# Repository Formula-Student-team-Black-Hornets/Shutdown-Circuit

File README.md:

# Shutdown Circuit Board

## Dimensions
* **Height:** 91.00 [mm]
* **Length:** 56.15 [mm]
* **Width:** ? [mm]

## Power supply
* **Voltage:** [V]
* **Current (max):** [A]
* **Current (min):** [A]
* **Current (avg):** [A]
* **Power:** [W]

## Connections

### J1
* **X.1** `[DOUT]` SDC_OUT
* **X.2** `[GND]`  GND
* **X.3** `[DIN]`  SDC_IN
* **X.3** `[GND]`  GND

### J2
* **X.1** `[DIN]`  RESET
* **X.2** `[VCC]`  12V
* **X.3** `[N.C]`  N.C
* **X.4** `[GND]`  GND

### J3
* **X.1** `[DOUT]` IMD_DASHBOARD
* **X.2** `[DOUT]` GND
* **X.3** `[DOUT]` AMS_DASHBOARD
* **X.4** `[DOUT]` GND

### J4
* **X.1** `[DIN]`  IMD_OkHS
* **X.2** `[GND]`  GND
* **X.3** `[DIN]`  BSPD
* **X.4** `[GND]`  GND

### J5
* **X.1** `[DIN]`  AMS_DISCHARGE_ENABLE
* **X.2** `[GND]`  GND
* **X.3** `[DIN]`  TSAL
* **X.4** `[GND]`  GND

### J6
* **X.1** `[VCC]`  12V
* **X.2** `[GND]`  GND
* **X.3** `[VCC]`  12V
* **X.4** `[GND]`  GND

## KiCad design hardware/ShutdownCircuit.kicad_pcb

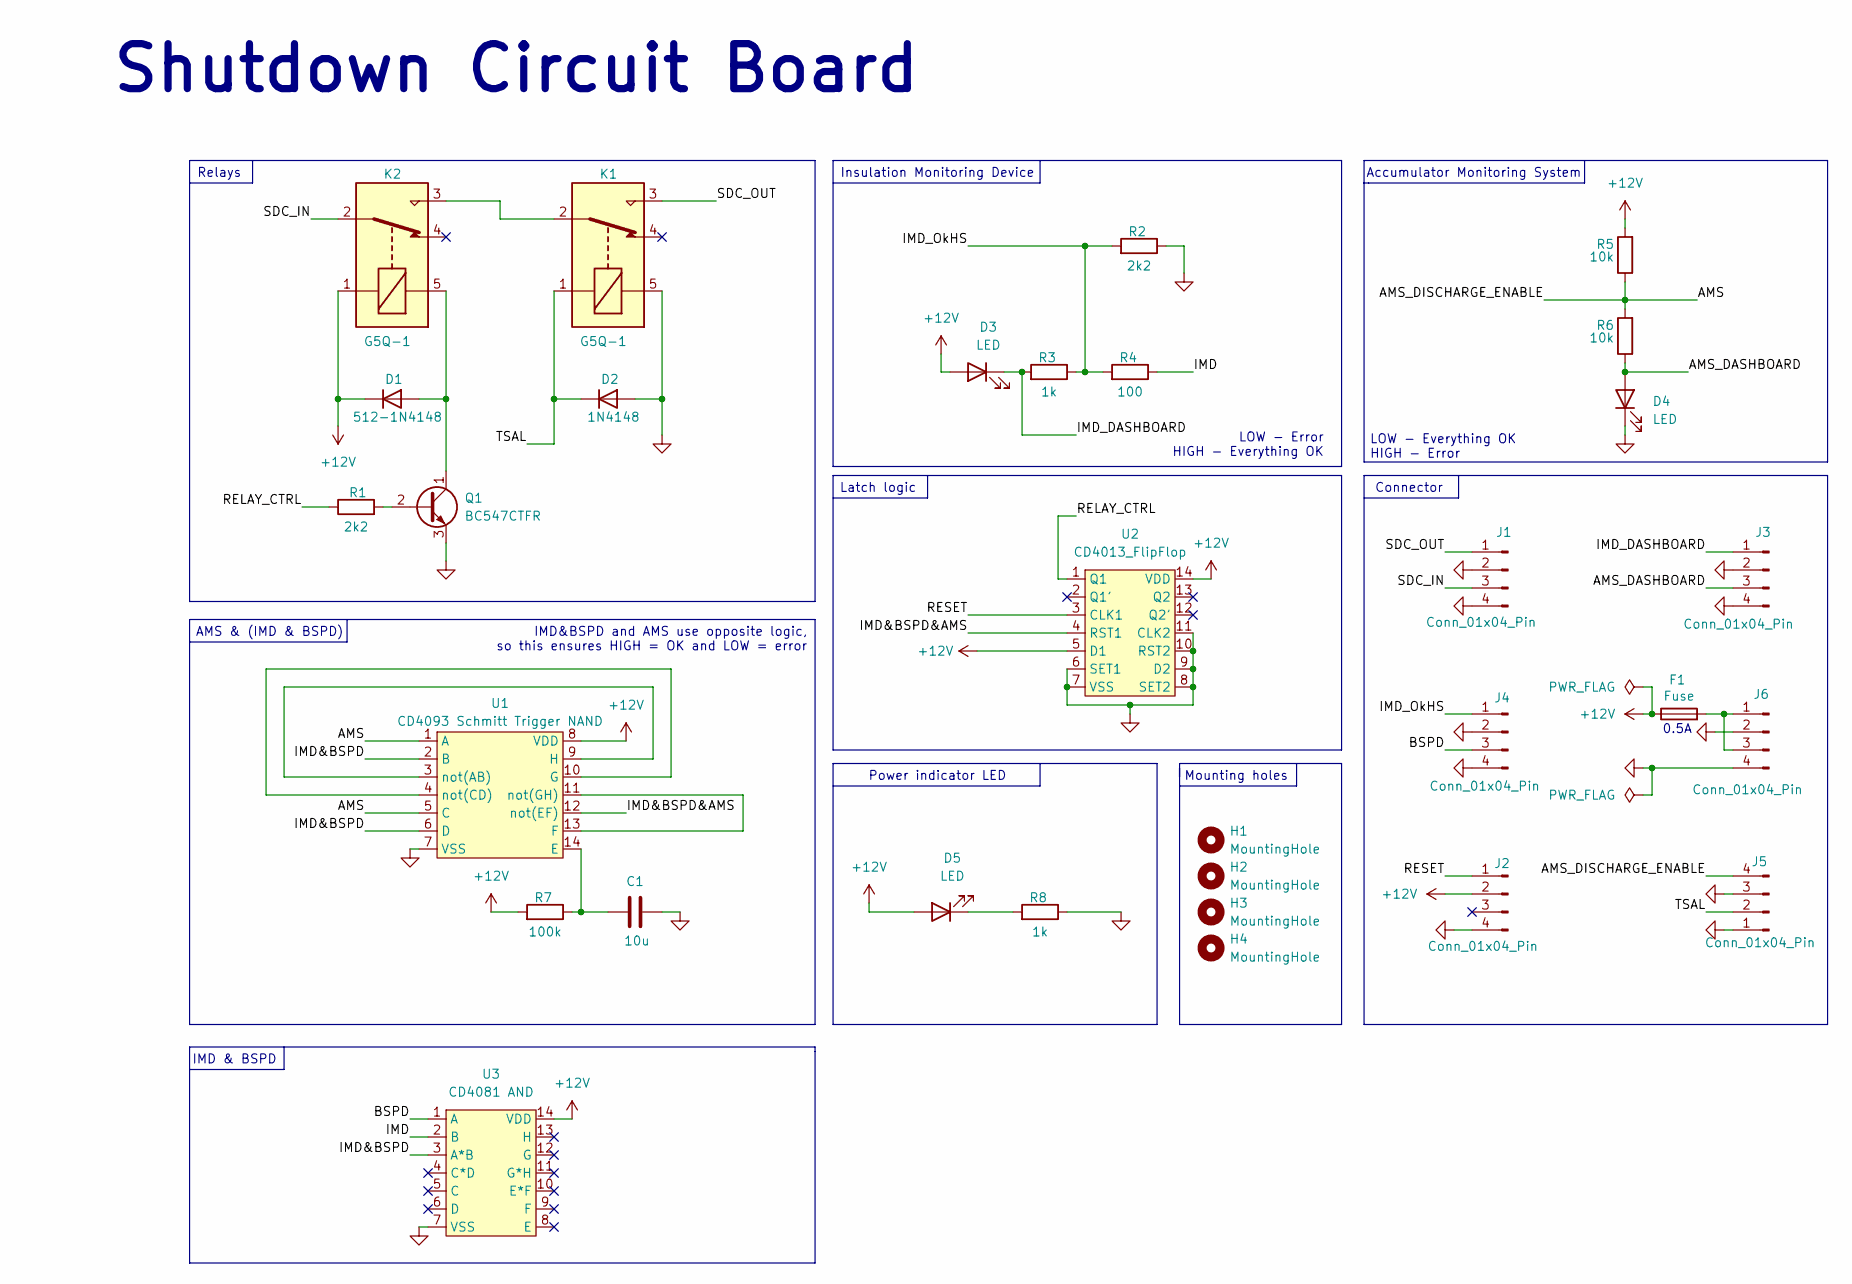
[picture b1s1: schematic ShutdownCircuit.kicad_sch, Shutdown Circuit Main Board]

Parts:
C1: 10u; C_1206_3216Metric_Pad1.33x1.80mm_HandSolder
D1: 512-1N4148; D_1206_3216Metric_Pad1.42x1.75mm_HandSolder
D2: 1N4148; D_1206_3216Metric_Pad1.42x1.75mm_HandSolder
D3, D4, D5: LED; LED_1206_3216Metric_Pad1.42x1.75mm_HandSolder
F1: Fuse; Fuse_1206_3216Metric_Pad1.42x1.75mm_HandSolder
H1, H2, H3, H4: MountingHole; MountingHole_2.1mm
J1, J2, J3, J4, J5, J6: Conn_01x04_Pin; Molex_Micro-Fit_3.0_43650-0400_1x04_P3.00mm_Horizontal
K1, K2: G5Q-1; Relay_SPDT_Omron-G5Q-1
Q1: BC547CTFR; TO-92_Inline
R1, R2: 2k2; R_1206_3216Metric_Pad1.30x1.75mm_HandSolder
R3, R8: 1k; R_1206_3216Metric_Pad1.30x1.75mm_HandSolder
R4: 100; R_1206_3216Metric_Pad1.30x1.75mm_HandSolder
R5, R6: 10k; R_1206_3216Metric_Pad1.30x1.75mm_HandSolder
R7: 100k; R_1206_3216Metric_Pad1.30x1.75mm_HandSolder
U1: CD4093 Schmitt Trigger NAND; SOIC-14_3.9x8.7mm_P1.27mm
U2: CD4013_FlipFlop; SOIC-14_3.9x8.7mm_P1.27mm
U3: CD4081 AND; SOIC-14_3.9x8.7mm_P1.27mm

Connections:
+12V: D1.1 (K), D3.2 (A), D5.2 (A), F1.1, J2.2, K2.1, R5.2, R7.2, U1.8 (VDD), U2.5 (D1), U2.14 (VDD), U3.14 (VDD)
/AMS: J5.4, R5.1, R6.2, U1.1 (A), U1.5 (C)
/AMS_DASHBOARD: D4.2 (A), J3.3, R6.1
/BSPD: J4.3, U3.1 (A)
/IMD: R4.1, U3.2 (B)
/IMD&BSPD: U1.2 (B), U1.6 (D), U3.3 (A*B)
/IMD&BSPD&AMS: U1.12 (not(EF)), U2.4 (RST1)
/IMD_DASHBOARD: D3.1 (K), J3.1, R3.2
/IMD_OkHS: J4.1, R2.2, R3.1, R4.2
/RELAY_CTRL: R1.1, U2.1 (Q1)
/RESET: J2.1, U2.3 (CLK1)
/SDC_IN: J1.3, K2.2
/SDC_OUT: J1.1, K1.3
/TSAL: D2.1 (K), J5.2, K1.1
GND: C1.2, D2.2 (A), D4.1 (K), J1.2, J1.4, J2.4, J3.2, J3.4, J4.2, J4.4, J5.1, J5.3, J6.2, J6.4, K1.5, Q1.3 (E), R2.1, R8.1, U1.7 (VSS), U2.6 (SET1), U2.7 (VSS), U2.8 (SET2), U2.9 (D2), U2.10 (RST2), U2.11 (CLK2), U3.7 (VSS)
unnamed: D1.2 (A), K2.5, Q1.1 (C)
unnamed: D5.1 (K), R8.2
unnamed: F1.2, J6.1, J6.3
unnamed: K1.2, K2.3
unnamed: Q1.2 (B), R1.2
unnamed: C1.1, R7.1, U1.14 (E)
unnamed: U1.11 (not(GH)), U1.13 (F)
unnamed: U1.4 (not(CD)), U1.10 (G)
unnamed: U1.3 (not(AB)), U1.9 (H)

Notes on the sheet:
0.5A
Insulation Monitoring Device
Shutdown Circuit Board
LOW - Everything OK HIGH - Error
Relays
Connector
IMD&BSPD and AMS use opposite logic, so this ensures HIGH = OK and LOW = error
Mounting holes
Latch logic
AMS & (IMD & BSPD)
LOW - Error HIGH - Everything OK
IMD & BSPD
Power indicator LED
Accumulator Monitoring System

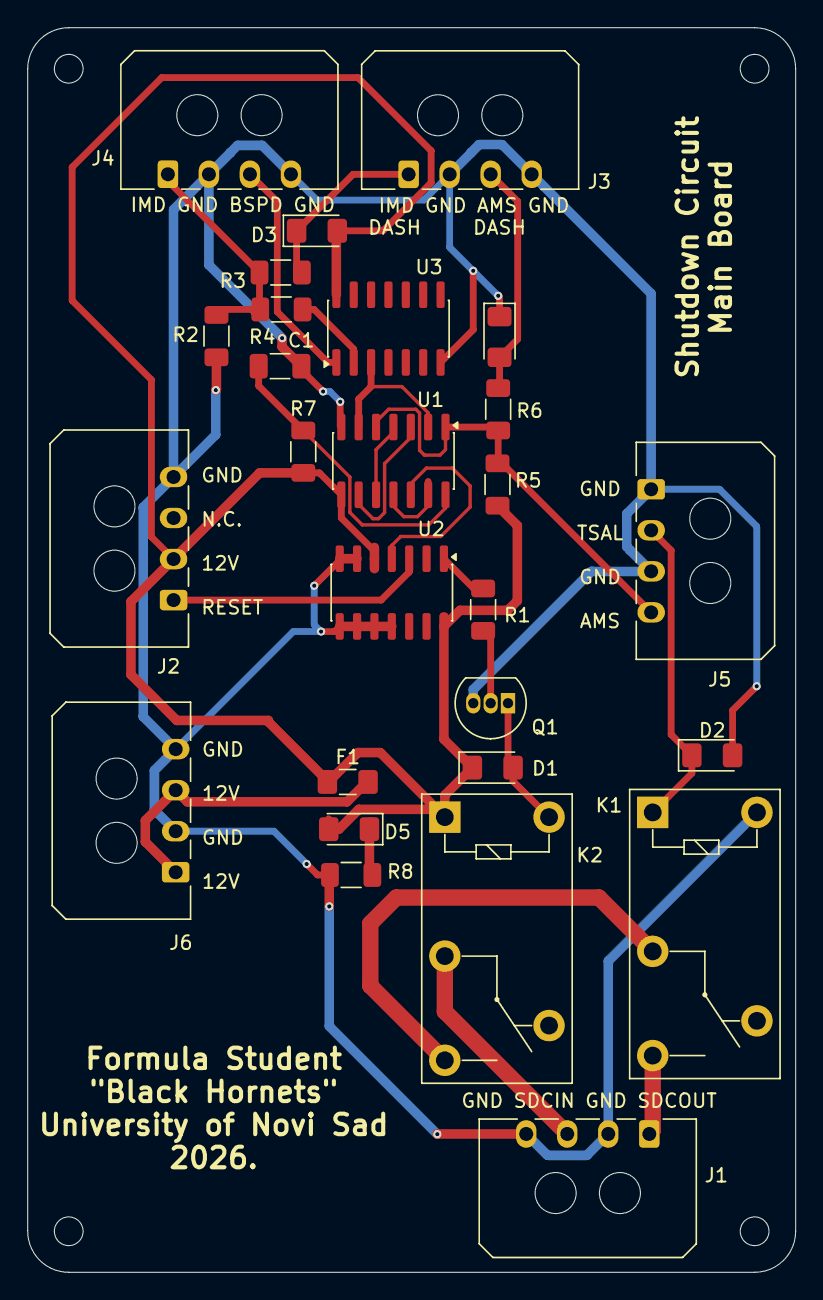
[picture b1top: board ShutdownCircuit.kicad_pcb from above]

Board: 2 copper layers, 56.1 x 91.0 mm, 31 parts (0 on the bottom side), 24 nets.

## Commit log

2026-04-25 Clean project structure and remove KiCad temp files
2026-05-05 PCB done
2026-05-05 Added text on PCB
2026-05-05 Minor traces fixes
2026-05-06 Traces fixed
2026-05-06 Documentasion fixes
2026-06-03 Fill zone deleted. Duddy fix it please
2026-06-03 Added Back layer GND Fill zone for the board
2026-06-03 Fuse -> HandSoldered
